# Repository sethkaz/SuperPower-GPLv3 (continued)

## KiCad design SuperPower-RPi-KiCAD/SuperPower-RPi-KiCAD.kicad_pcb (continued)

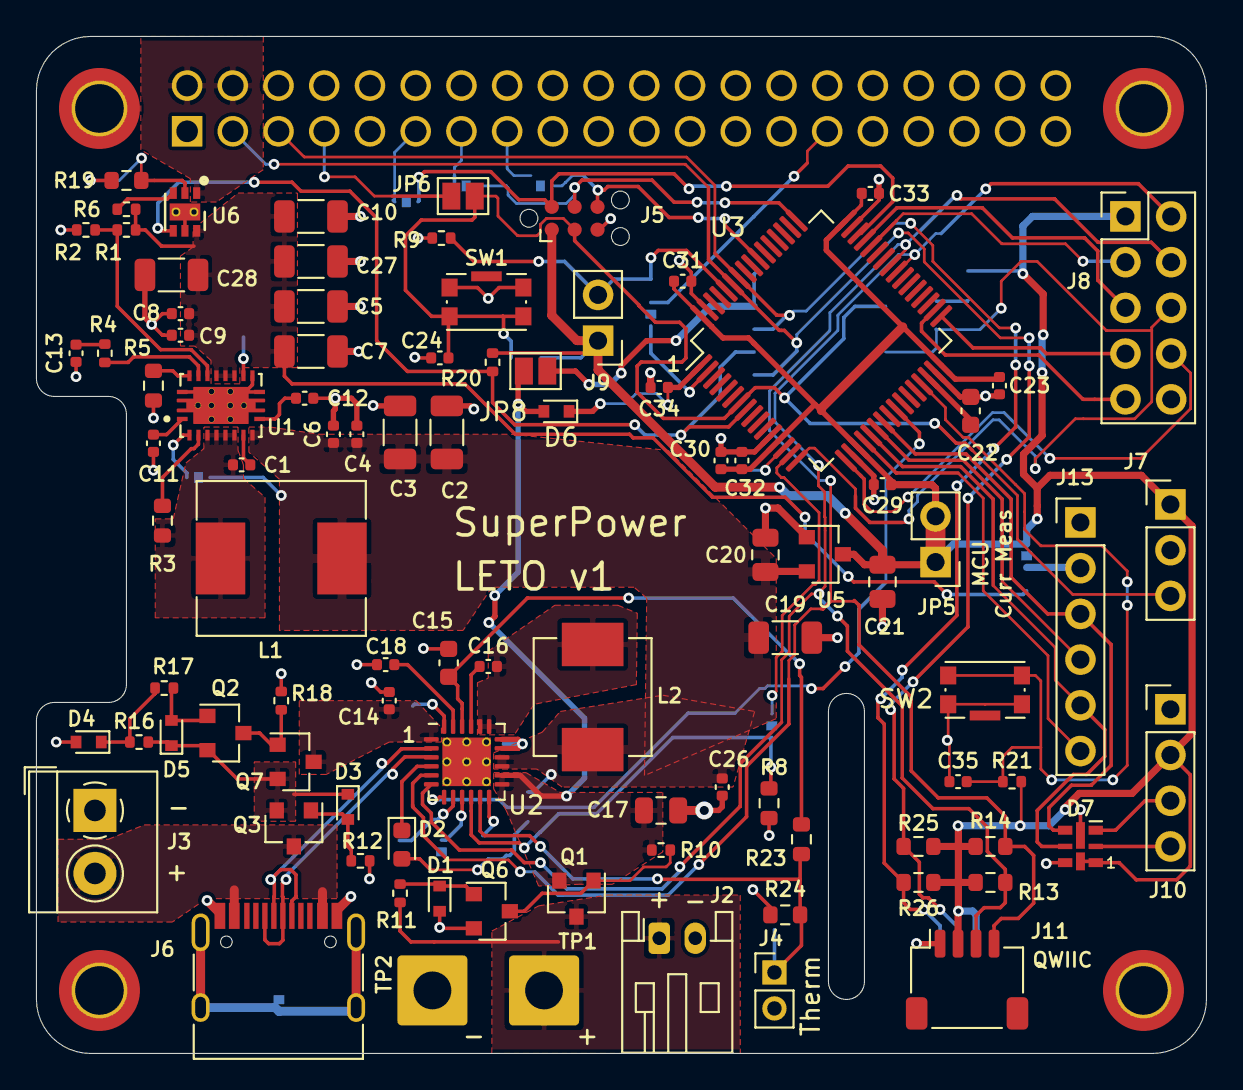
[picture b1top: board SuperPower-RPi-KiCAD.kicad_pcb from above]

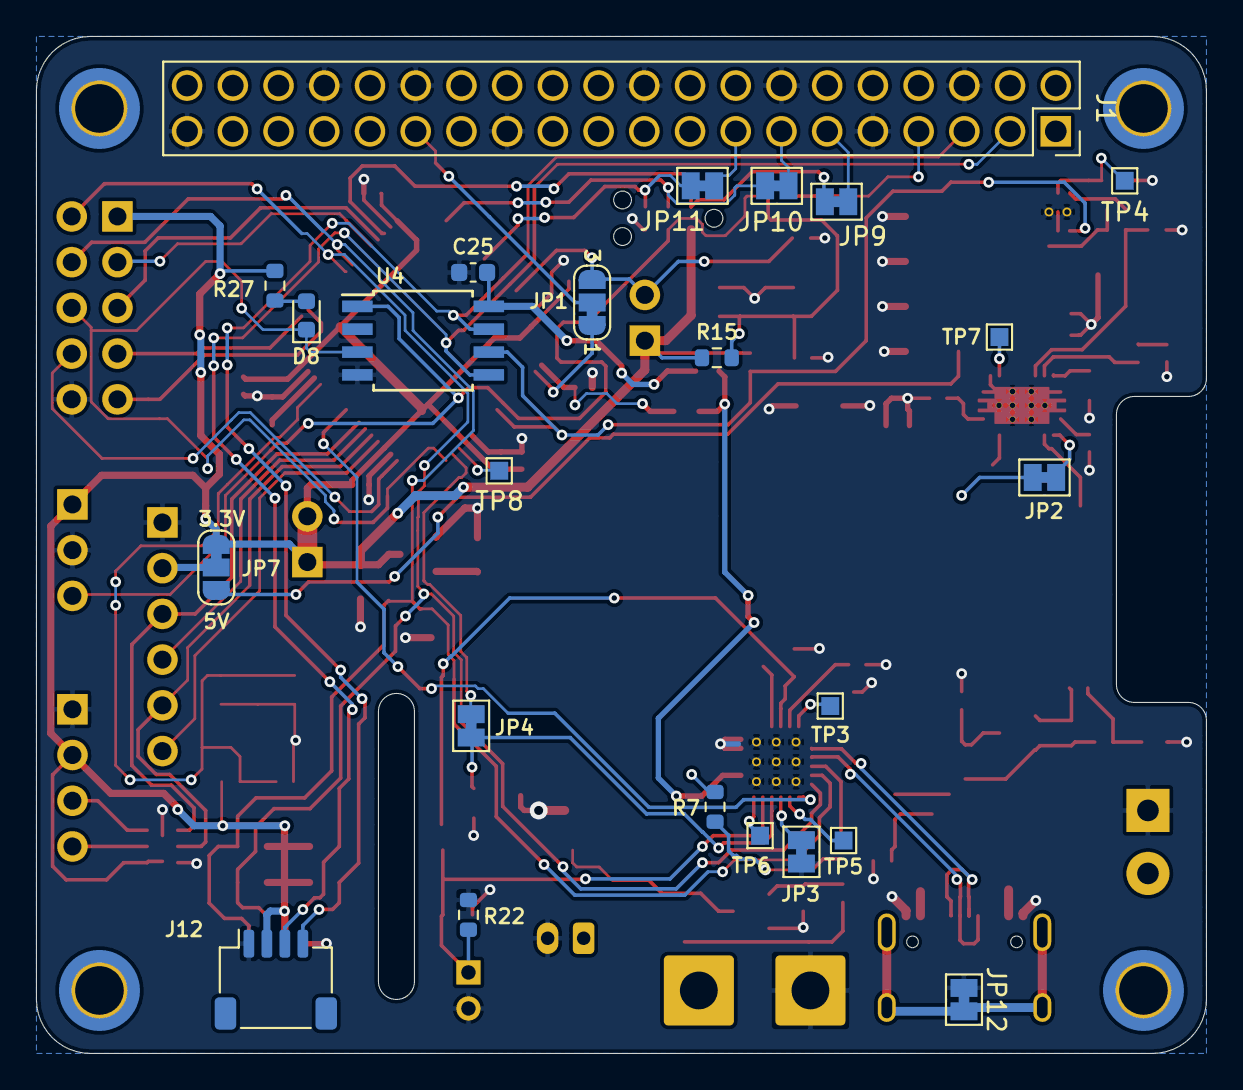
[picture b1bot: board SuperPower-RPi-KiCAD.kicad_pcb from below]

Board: 2 copper layers, 65.0 x 56.5 mm, 122 parts (24 on the bottom side), 82 nets.

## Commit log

2021-01-24 Added snapshot of project under GPLv3
2021-01-29 Final prep for distribution to KiCAD folks.
2021-01-29 Removed logo file.
2021-02-07 Non-change to test git.
2021-02-07 Updated to KiCAD v5.99 (and undid the non-change)
2021-02-07 Updated symbol library to v5.99 format.
